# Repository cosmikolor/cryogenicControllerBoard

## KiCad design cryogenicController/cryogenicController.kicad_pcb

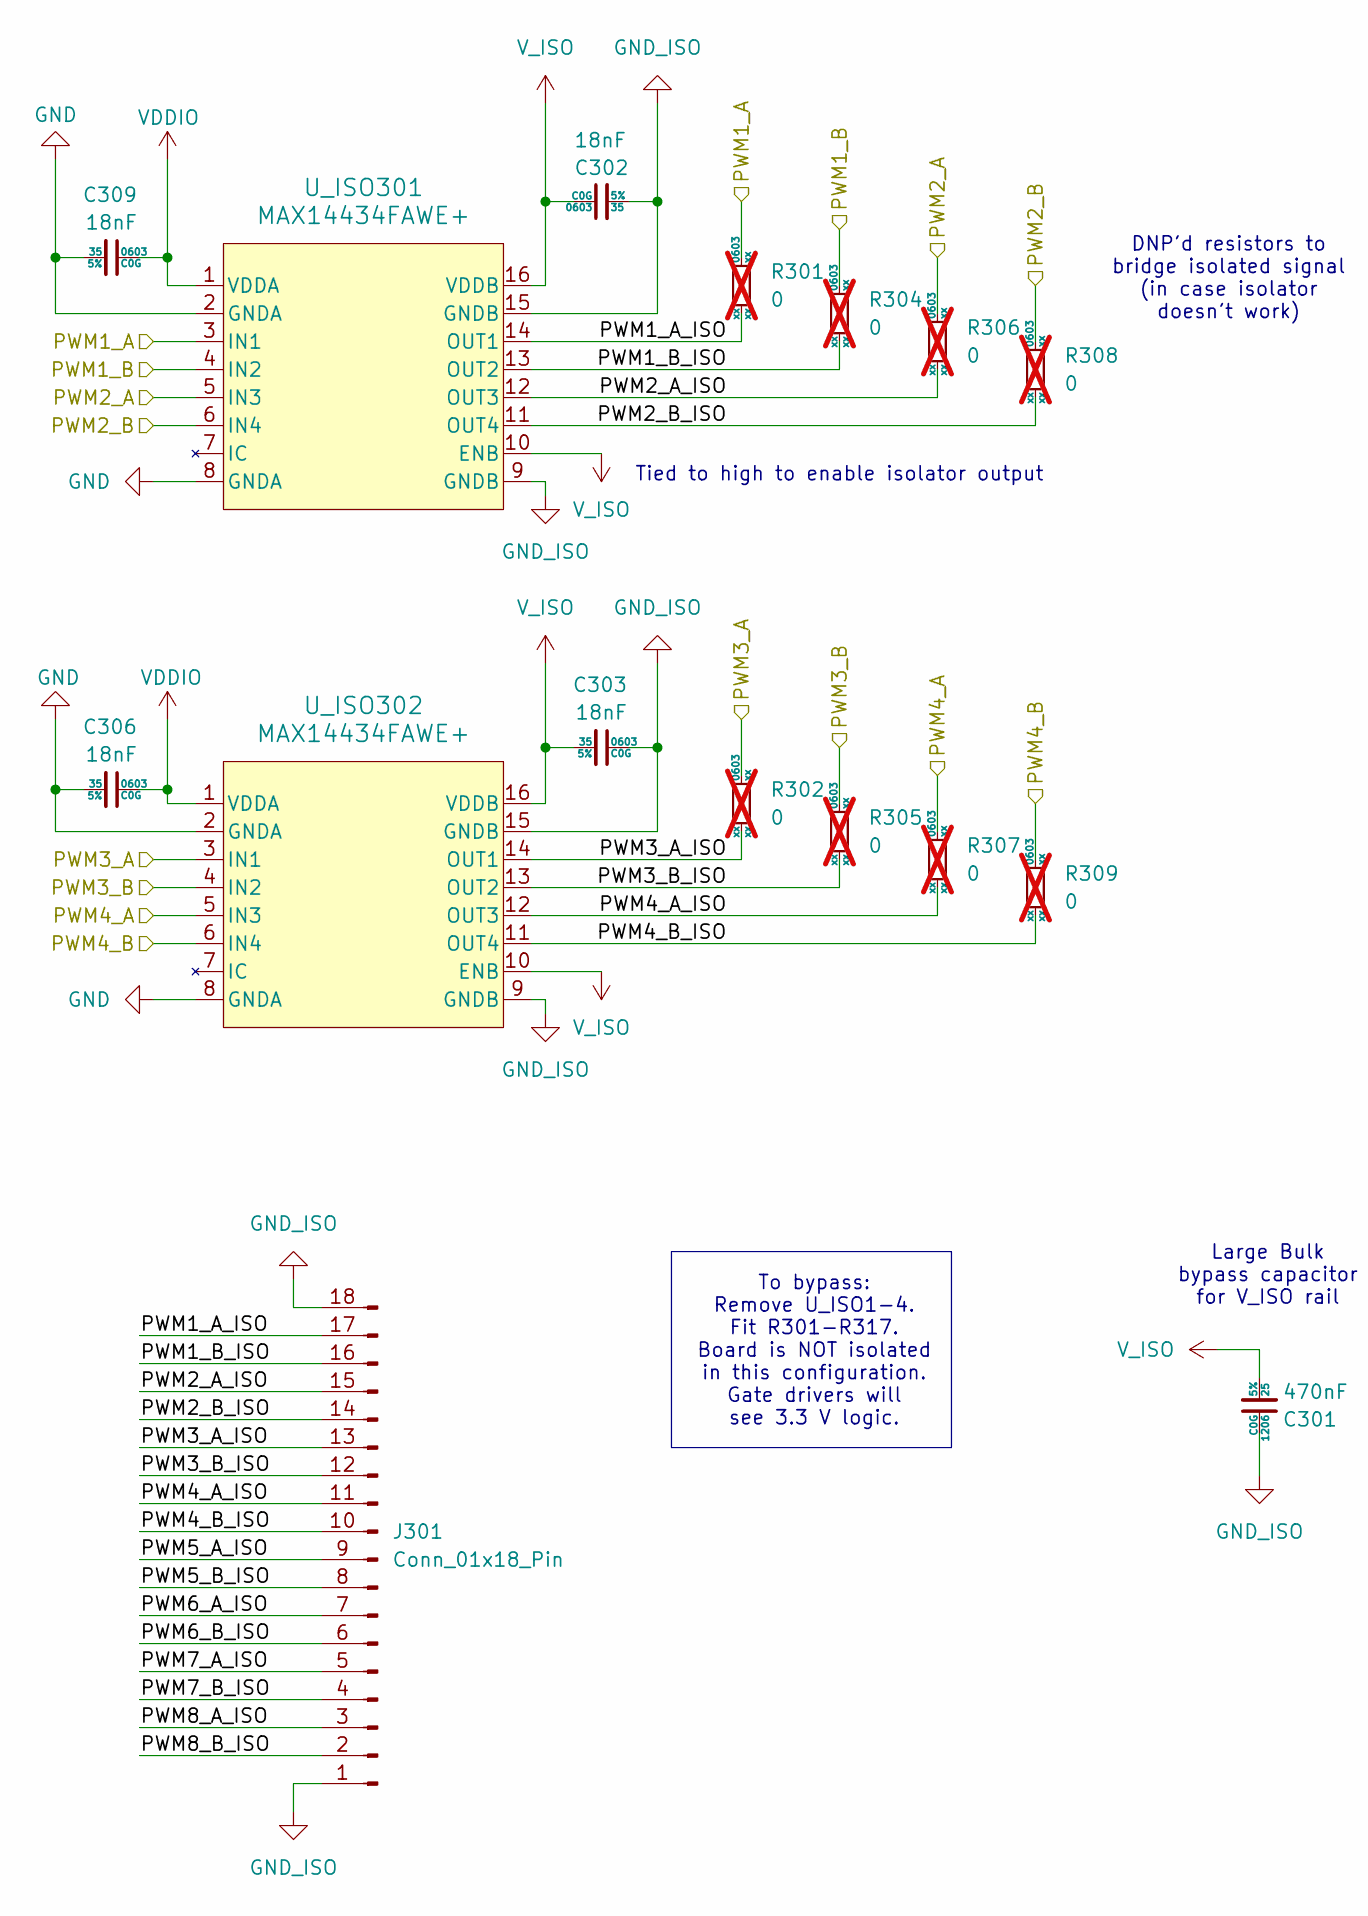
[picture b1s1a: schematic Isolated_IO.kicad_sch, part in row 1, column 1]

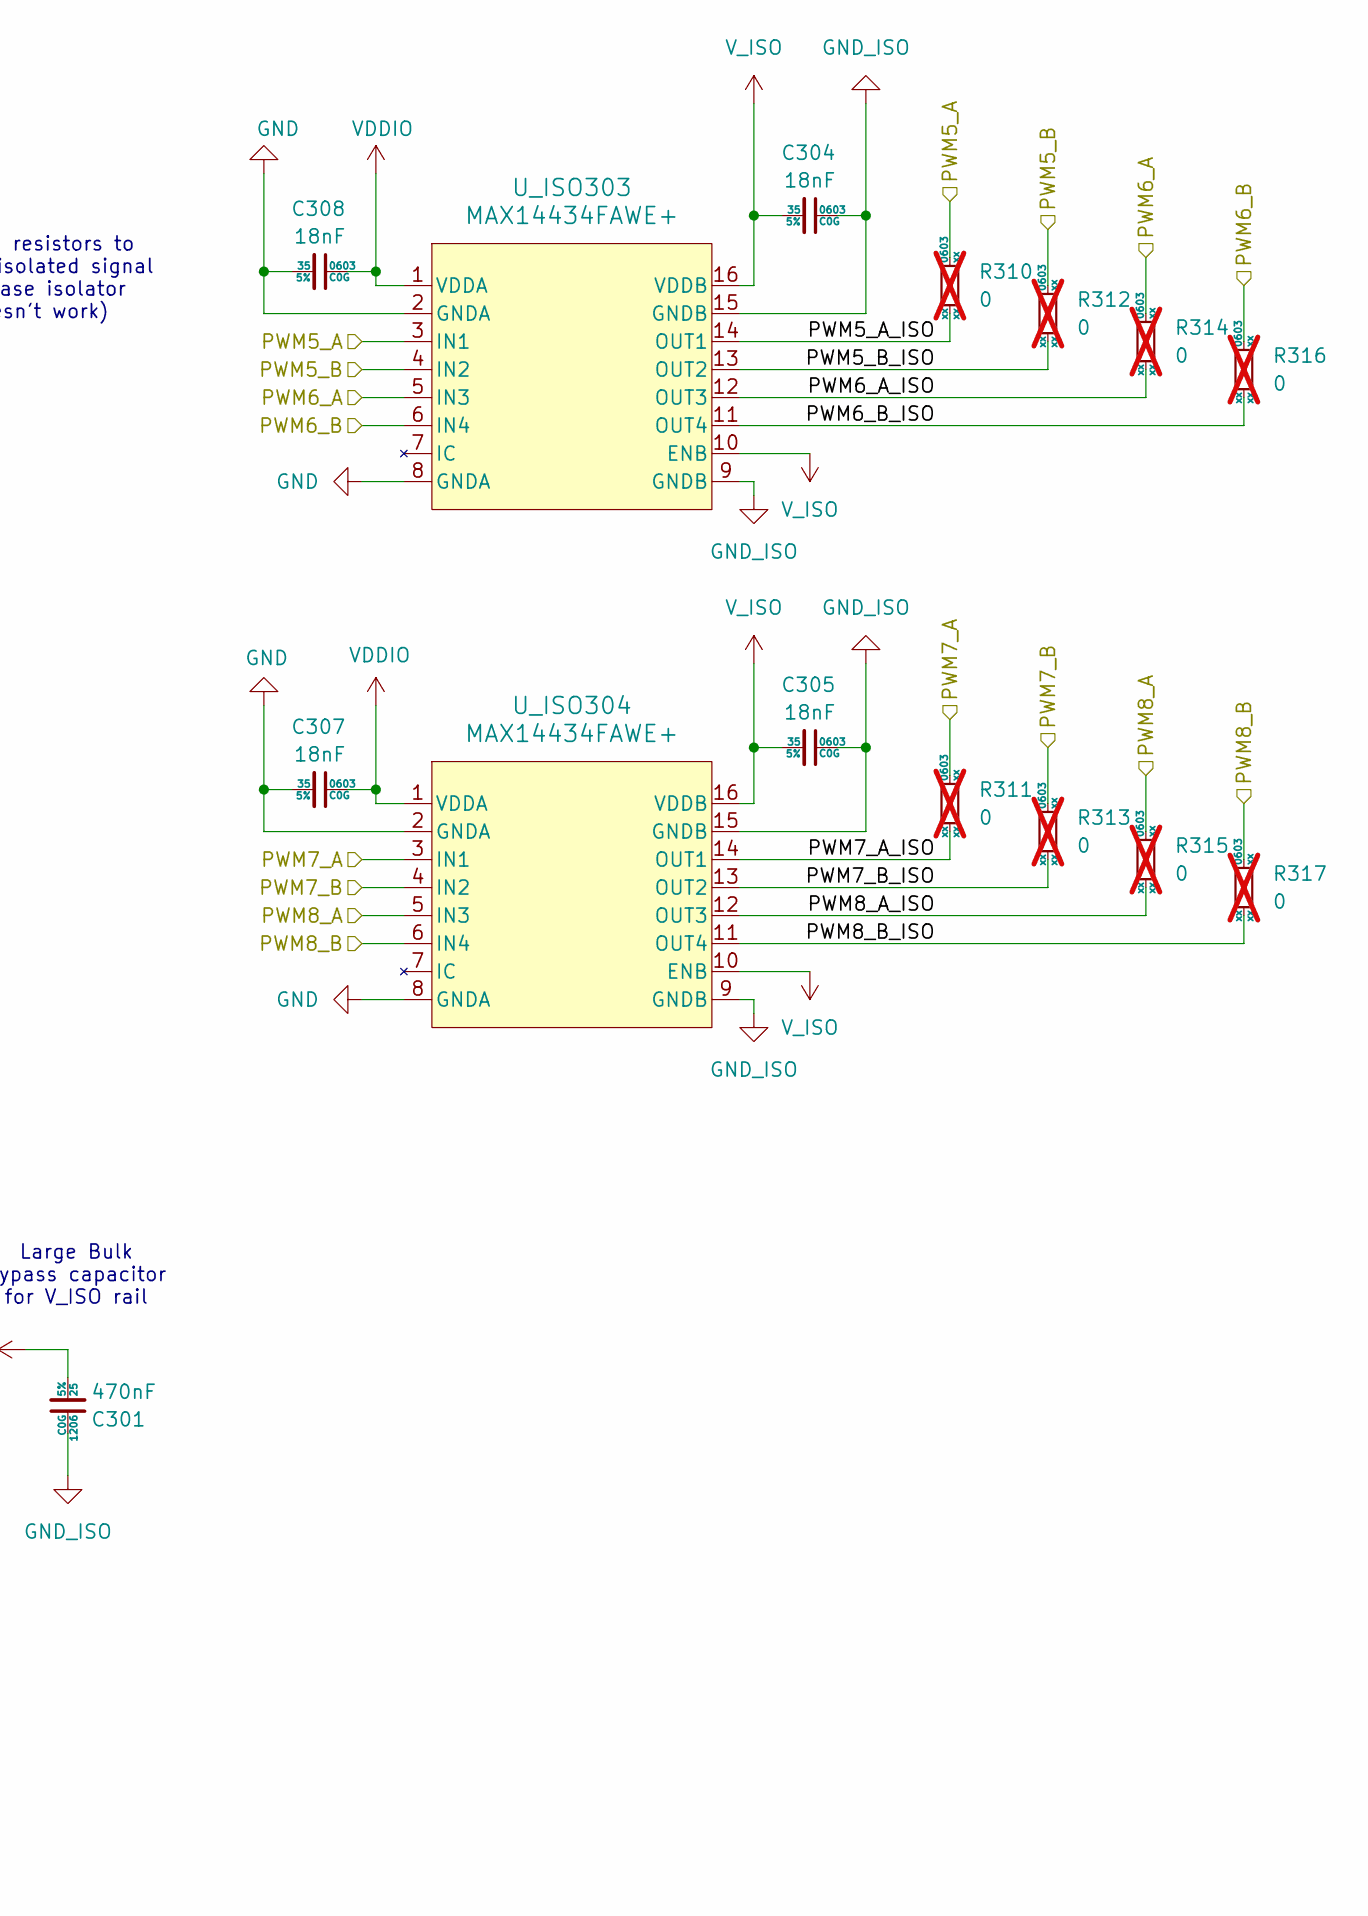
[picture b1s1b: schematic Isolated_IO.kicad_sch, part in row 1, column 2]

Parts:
C301: 470nF; C_1206_3216Metric; Voltage 25; Tolerance 5%; MfrPN GRM31C5C1E474JE01L
C302, C303, C304, C305, C306, C307, C308, C309: 18nF; C_0603_1608Metric; Voltage 35; Tolerance 5%; MfrPN C1608C0G1V183J080AC
J301: Conn_01x18_Pin; PinHeader_1x18_P2.54mm_Vertical
R301, R302, R304, R305, R306, R307, R308, R309, R310, R311, R312, R313, R314, R315, R316, R317: 0; R_1206_3216Metric; Tolerance xx; Voltage xx; not fitted
U_ISO301, U_ISO302, U_ISO303, U_ISO304: MAX14434FAWE+; SOIC-16W_7.5x10.3mm_P1.27mm

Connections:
/Isolated_IO/PWM1_A: R301.2, U_ISO301.3 (IN1); also elsewhere on the board
/Isolated_IO/PWM1_A_ISO: J301.17, R301.1, U_ISO301.14 (OUT1)
/Isolated_IO/PWM1_B: R304.2, U_ISO301.4 (IN2); also elsewhere on the board
/Isolated_IO/PWM1_B_ISO: J301.16, R304.1, U_ISO301.13 (OUT2)
/Isolated_IO/PWM2_A: R306.2, U_ISO301.5 (IN3); also elsewhere on the board
/Isolated_IO/PWM2_A_ISO: J301.15, R306.1, U_ISO301.12 (OUT3)
/Isolated_IO/PWM2_B: R308.2, U_ISO301.6 (IN4); also elsewhere on the board
/Isolated_IO/PWM2_B_ISO: J301.14, R308.1, U_ISO301.11 (OUT4)
/Isolated_IO/PWM3_A: R302.2, U_ISO302.3 (IN1); also elsewhere on the board
/Isolated_IO/PWM3_A_ISO: J301.13, R302.1, U_ISO302.14 (OUT1)
/Isolated_IO/PWM3_B: R305.2, U_ISO302.4 (IN2); also elsewhere on the board
/Isolated_IO/PWM3_B_ISO: J301.12, R305.1, U_ISO302.13 (OUT2)
/Isolated_IO/PWM4_A: R307.2, U_ISO302.5 (IN3); also elsewhere on the board
/Isolated_IO/PWM4_A_ISO: J301.11, R307.1, U_ISO302.12 (OUT3)
/Isolated_IO/PWM4_B: R309.2, U_ISO302.6 (IN4); also elsewhere on the board
/Isolated_IO/PWM4_B_ISO: J301.10, R309.1, U_ISO302.11 (OUT4)
/Isolated_IO/PWM5_A: R310.2, U_ISO303.3 (IN1); also elsewhere on the board
/Isolated_IO/PWM5_A_ISO: J301.9, R310.1, U_ISO303.14 (OUT1)
/Isolated_IO/PWM5_B: R312.2, U_ISO303.4 (IN2); also elsewhere on the board
/Isolated_IO/PWM5_B_ISO: J301.8, R312.1, U_ISO303.13 (OUT2)
/Isolated_IO/PWM6_A: R314.2, U_ISO303.5 (IN3); also elsewhere on the board
/Isolated_IO/PWM6_A_ISO: J301.7, R314.1, U_ISO303.12 (OUT3)
/Isolated_IO/PWM6_B: R316.2, U_ISO303.6 (IN4); also elsewhere on the board
/Isolated_IO/PWM6_B_ISO: J301.6, R316.1, U_ISO303.11 (OUT4)
/Isolated_IO/PWM7_A: R311.2, U_ISO304.3 (IN1); also elsewhere on the board
/Isolated_IO/PWM7_A_ISO: J301.5, R311.1, U_ISO304.14 (OUT1)
/Isolated_IO/PWM7_B: R313.2, U_ISO304.4 (IN2); also elsewhere on the board
/Isolated_IO/PWM7_B_ISO: J301.4, R313.1, U_ISO304.13 (OUT2)
/Isolated_IO/PWM8_A: R315.2, U_ISO304.5 (IN3); also elsewhere on the board
/Isolated_IO/PWM8_A_ISO: J301.3, R315.1, U_ISO304.12 (OUT3)
/Isolated_IO/PWM8_B: R317.2, U_ISO304.6 (IN4); also elsewhere on the board
/Isolated_IO/PWM8_B_ISO: J301.2, R317.1, U_ISO304.11 (OUT4)
GND: C306.2, C307.2, C308.2, C309.2, U_ISO301.2 (GNDA), U_ISO301.8 (GNDA), U_ISO302.2 (GNDA), U_ISO302.8 (GNDA), U_ISO303.2 (GNDA), U_ISO303.8 (GNDA), U_ISO304.2 (GNDA), U_ISO304.8 (GNDA); also elsewhere on the board
GND_ISO: C301.1, C302.2, C303.1, C304.1, C305.1, J301.1, J301.18, U_ISO301.9 (GNDB), U_ISO301.15 (GNDB), U_ISO302.9 (GNDB), U_ISO302.15 (GNDB), U_ISO303.9 (GNDB), U_ISO303.15 (GNDB), U_ISO304.9 (GNDB), U_ISO304.15 (GNDB); also elsewhere on the board
VDDIO: C306.1, C307.1, C308.1, C309.1, U_ISO301.1 (VDDA), U_ISO302.1 (VDDA), U_ISO303.1 (VDDA), U_ISO304.1 (VDDA); also elsewhere on the board
V_ISO: C301.2, C302.1, C303.2, C304.2, C305.2, U_ISO301.10 (ENB), U_ISO301.16 (VDDB), U_ISO302.10 (ENB), U_ISO302.16 (VDDB), U_ISO303.10 (ENB), U_ISO303.16 (VDDB), U_ISO304.10 (ENB), U_ISO304.16 (VDDB); also elsewhere on the board

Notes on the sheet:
DNP'd resistors to bridge isolated signal (in case isolator doesn't work)
To bypass: Remove U_ISO1-4. Fit R301-R317. Board is NOT isolated in this configuration. Gate drivers will see 3.3 V logic.
Tied to high to enable isolator output
Large Bulk bypass capacitor for V_ISO rail

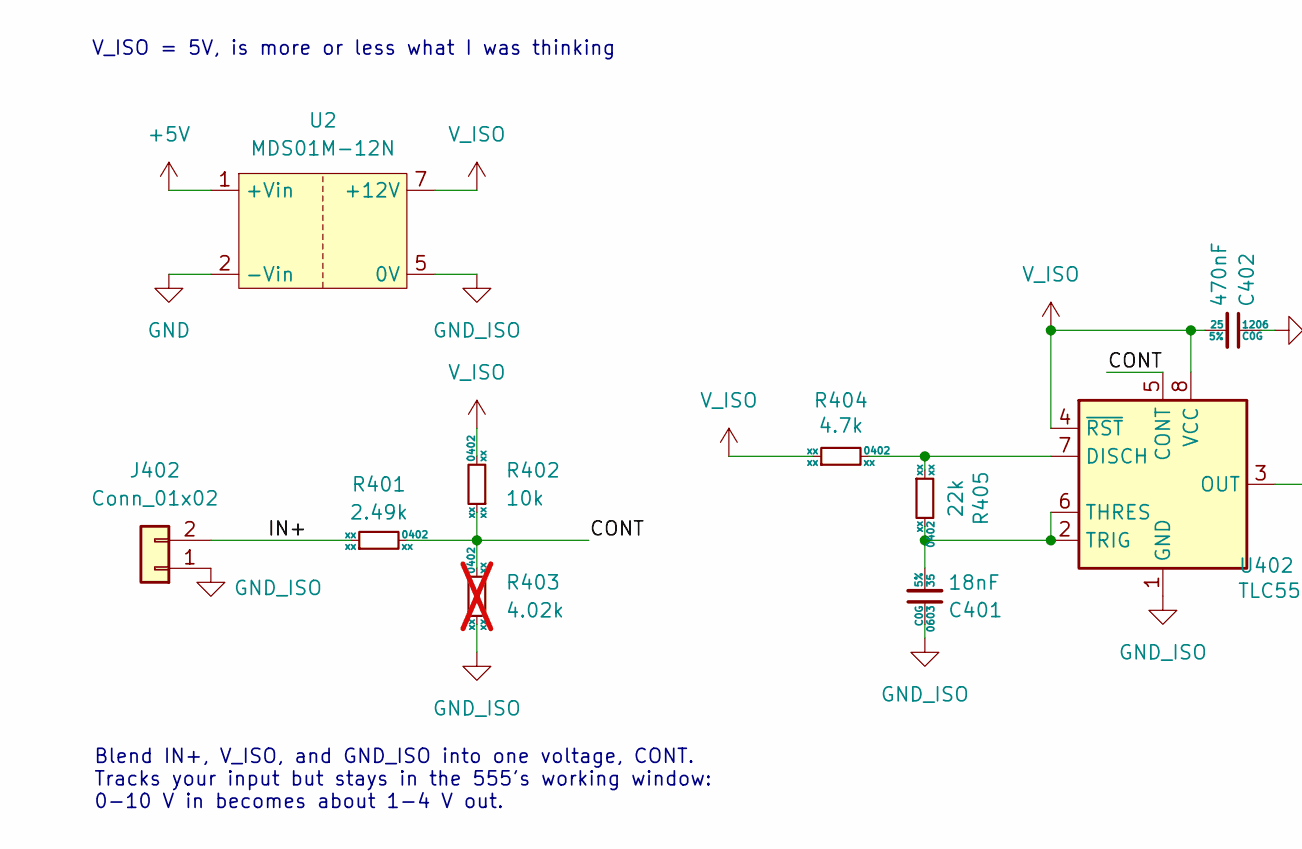
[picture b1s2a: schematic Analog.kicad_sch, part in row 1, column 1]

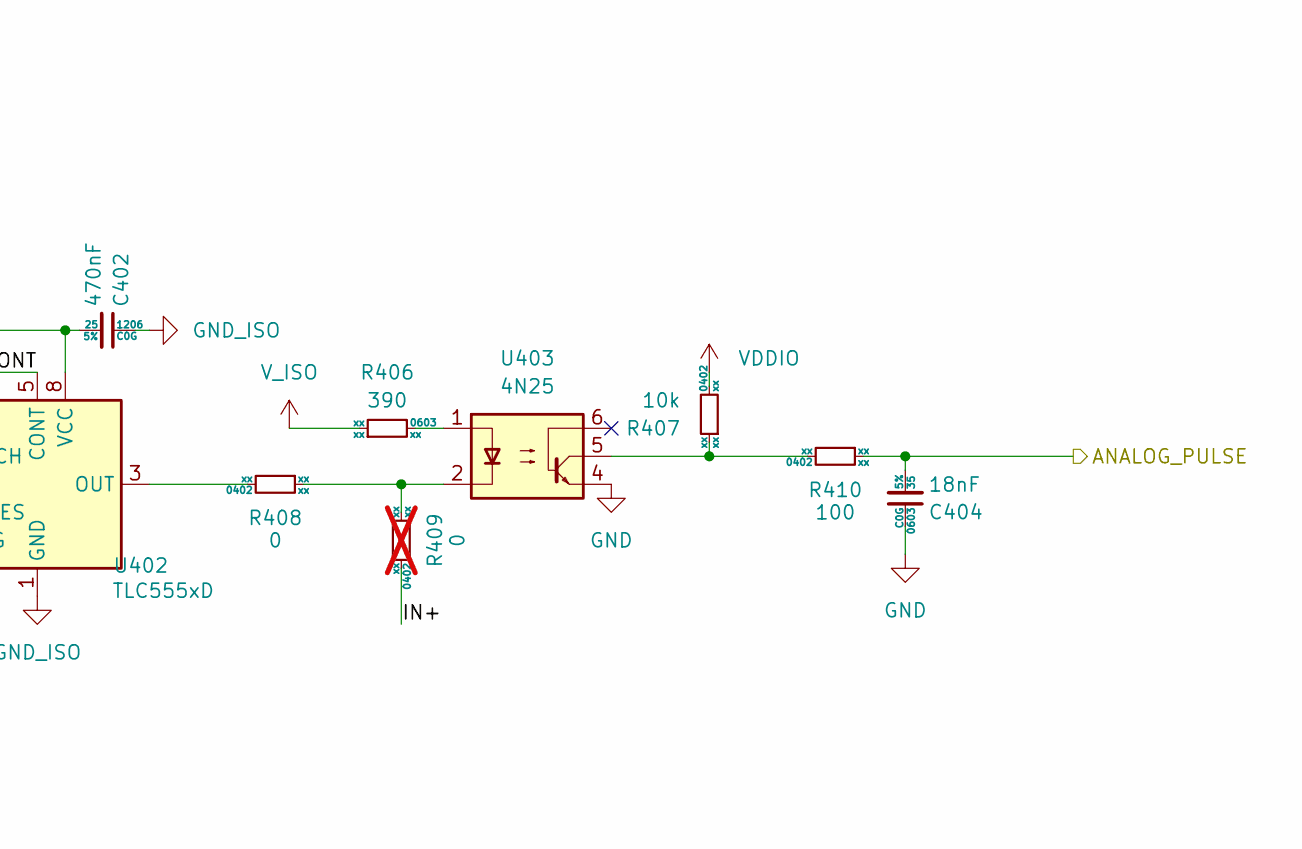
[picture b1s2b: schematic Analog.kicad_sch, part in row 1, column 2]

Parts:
C401, C404: 18nF; C_0603_1608Metric; Voltage 35; Tolerance 5%
C402: 470nF; C_1206_3216Metric; Voltage 25; Tolerance 5%; MfrPN GRM31C5C1E474JE01L
J402: Conn_01x02; PinHeader_1x02_P2.54mm_Vertical
R401: 2.49k; R_0402_1005Metric; Tolerance xx; Voltage xx
R402, R407: 10k; R_0402_1005Metric; Tolerance xx; Voltage xx
R403: 4.02k; R_0402_1005Metric; Tolerance xx; Voltage xx; not fitted
R404: 4.7k; R_0402_1005Metric; Tolerance xx; Voltage xx
R405: 22k; R_0402_1005Metric; Tolerance xx; Voltage xx
R406: 390; R_0402_1005Metric; Tolerance xx; Voltage xx
R408: 0; R_0402_1005Metric; Tolerance xx; Voltage xx
R409: 0; R_0402_1005Metric; Tolerance xx; Voltage xx; not fitted
R410: 100; R_0402_1005Metric; Tolerance xx; Voltage xx
U2: MDS01M-12N
U402: TLC555xD; SOIC-8_3.9x4.9mm_P1.27mm
U403: 4N25; DIP-6_W7.62mm

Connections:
+5V: U2.1 (+Vin)
/Analog/ANALOG_PULSE: C404.2, R410.1; also elsewhere on the board
/Analog/CONT: R401.2, R402.1, R403.2, U402.5 (CONT)
/Analog/IN+: J402.2, R401.1, R409.2
GND: C404.1, U2.2 (-Vin), U403.4; also elsewhere on the board
GND_ISO: C401.1, C402.1, J402.1, R403.1, U2.5 (0V), U402.1 (GND); also elsewhere on the board
unnamed: R406.2, U403.1
unnamed: R407.1, R410.2, U403.5
unnamed: R408.1, R409.1, U403.2
unnamed: R404.2, R405.1, U402.7 (DISCH)
unnamed: R408.2, U402.3 (OUT)
unnamed: C401.2, R405.2, U402.2 (TRIG), U402.6 (THRES)
VDDIO: R407.2; also elsewhere on the board
V_ISO: C402.2, R402.2, R404.1, R406.1, U2.7 (+12V), U402.4 (~RST), U402.8 (VCC); also elsewhere on the board

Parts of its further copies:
C403, C406, C407, C409: 18nF; C_0603_1608Metric; Voltage 35; Tolerance 5%
C405, C408: 470nF; C_1206_3216Metric; Voltage 25; Tolerance 5%; MfrPN GRM31C5C1E474JE01L
J403, J404: Conn_01x02; PinHeader_1x02_P2.54mm_Vertical
R411, R421: 2.49k; R_0402_1005Metric; Tolerance xx; Voltage xx
R412, R419, R422, R429: 10k; R_0402_1005Metric; Tolerance xx; Voltage xx
R413, R423: 4.02k; R_0402_1005Metric; Tolerance xx; Voltage xx; not fitted
R414, R424: 4.7k; R_0402_1005Metric; Tolerance xx; Voltage xx
R415, R425: 22k; R_0402_1005Metric; Tolerance xx; Voltage xx
R416, R426: 0; R_0402_1005Metric; Tolerance xx; Voltage xx
R417, R427: 390; R_0402_1005Metric; Tolerance xx; Voltage xx
R418, R428: 0; R_0402_1005Metric; Tolerance xx; Voltage xx; not fitted
R420, R430: 100; R_0402_1005Metric; Tolerance xx; Voltage xx
U404, U406: TLC555xD; SOIC-8_3.9x4.9mm_P1.27mm
U405, U407: 4N25; DIP-6_W7.62mm

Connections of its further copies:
/Analog1/ANALOG_PULSE: C406.2, R420.1; also elsewhere on the board
/Analog1/CONT: R411.2, R412.1, R413.2, U404.5 (CONT)
/Analog1/IN+: J403.2, R411.1, R418.2
/Analog2/ANALOG_PULSE: C409.2, R430.1; also elsewhere on the board
/Analog2/CONT: R421.2, R422.1, R423.2, U406.5 (CONT)
/Analog2/IN+: J404.2, R421.1, R428.2
GND: C406.1, C409.1, U405.4, U407.4; also elsewhere on the board
GND_ISO: C403.1, C405.1, C407.1, C408.1, J403.1, J404.1, R413.1, R423.1, U404.1 (GND), U406.1 (GND); also elsewhere on the board
unnamed: R416.1, R418.1, U405.2
unnamed: R417.2, U405.1
unnamed: R419.1, R420.2, U405.5
unnamed: R426.1, R428.1, U407.2
unnamed: R427.2, U407.1
unnamed: R429.1, R430.2, U407.5
unnamed: R414.2, R415.1, U404.7 (DISCH)
unnamed: R416.2, U404.3 (OUT)
unnamed: C403.2, R415.2, U404.2 (TRIG), U404.6 (THRES)
unnamed: R424.2, R425.1, U406.7 (DISCH)
unnamed: R426.2, U406.3 (OUT)
unnamed: C407.2, R425.2, U406.2 (TRIG), U406.6 (THRES)
VDDIO: R419.2, R429.2; also elsewhere on the board
V_ISO: C405.2, C408.2, R412.2, R414.1, R417.1, R422.2, R424.1, R427.1, U404.4 (~RST), U404.8 (VCC), U406.4 (~RST), U406.8 (VCC); also elsewhere on the board

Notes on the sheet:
Blend IN+, V_ISO, and GND_ISO into one voltage, CONT. Tracks your input but stays in the 555's working window: 0-10 V in becomes about 1-4 V out.
V_ISO = 5V, is more or less what I was thinking

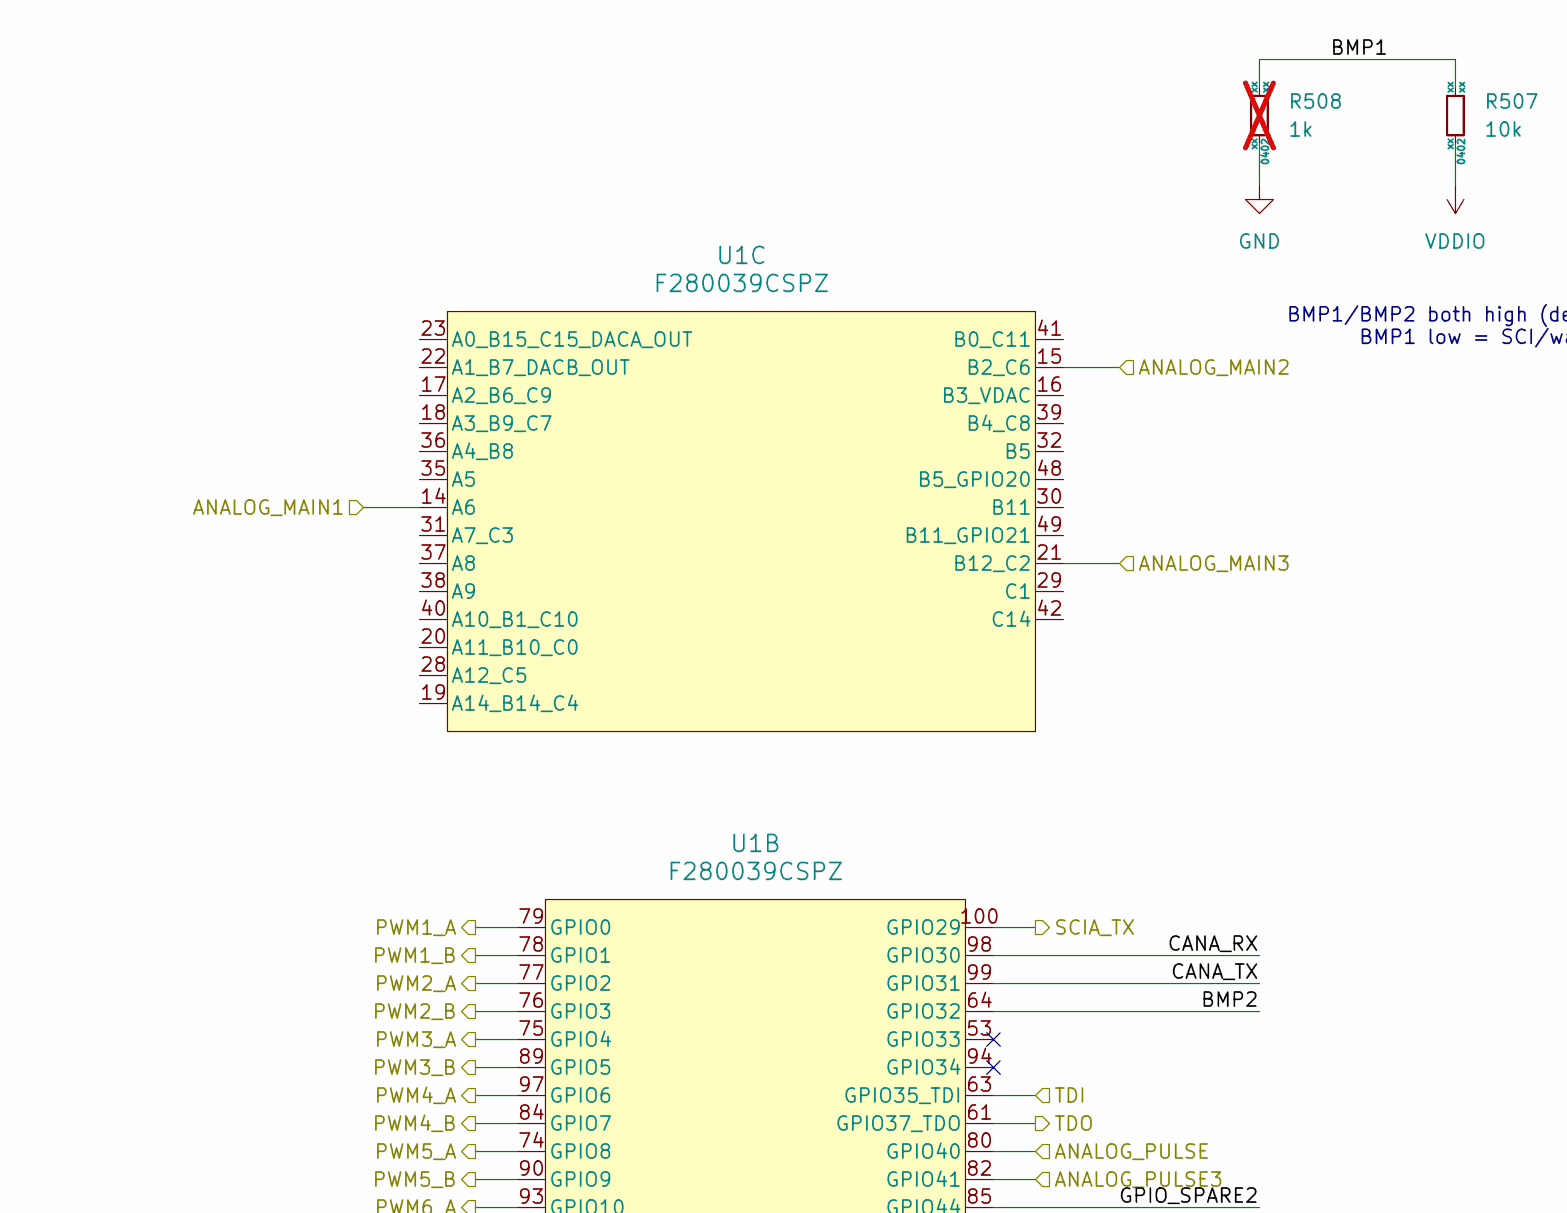
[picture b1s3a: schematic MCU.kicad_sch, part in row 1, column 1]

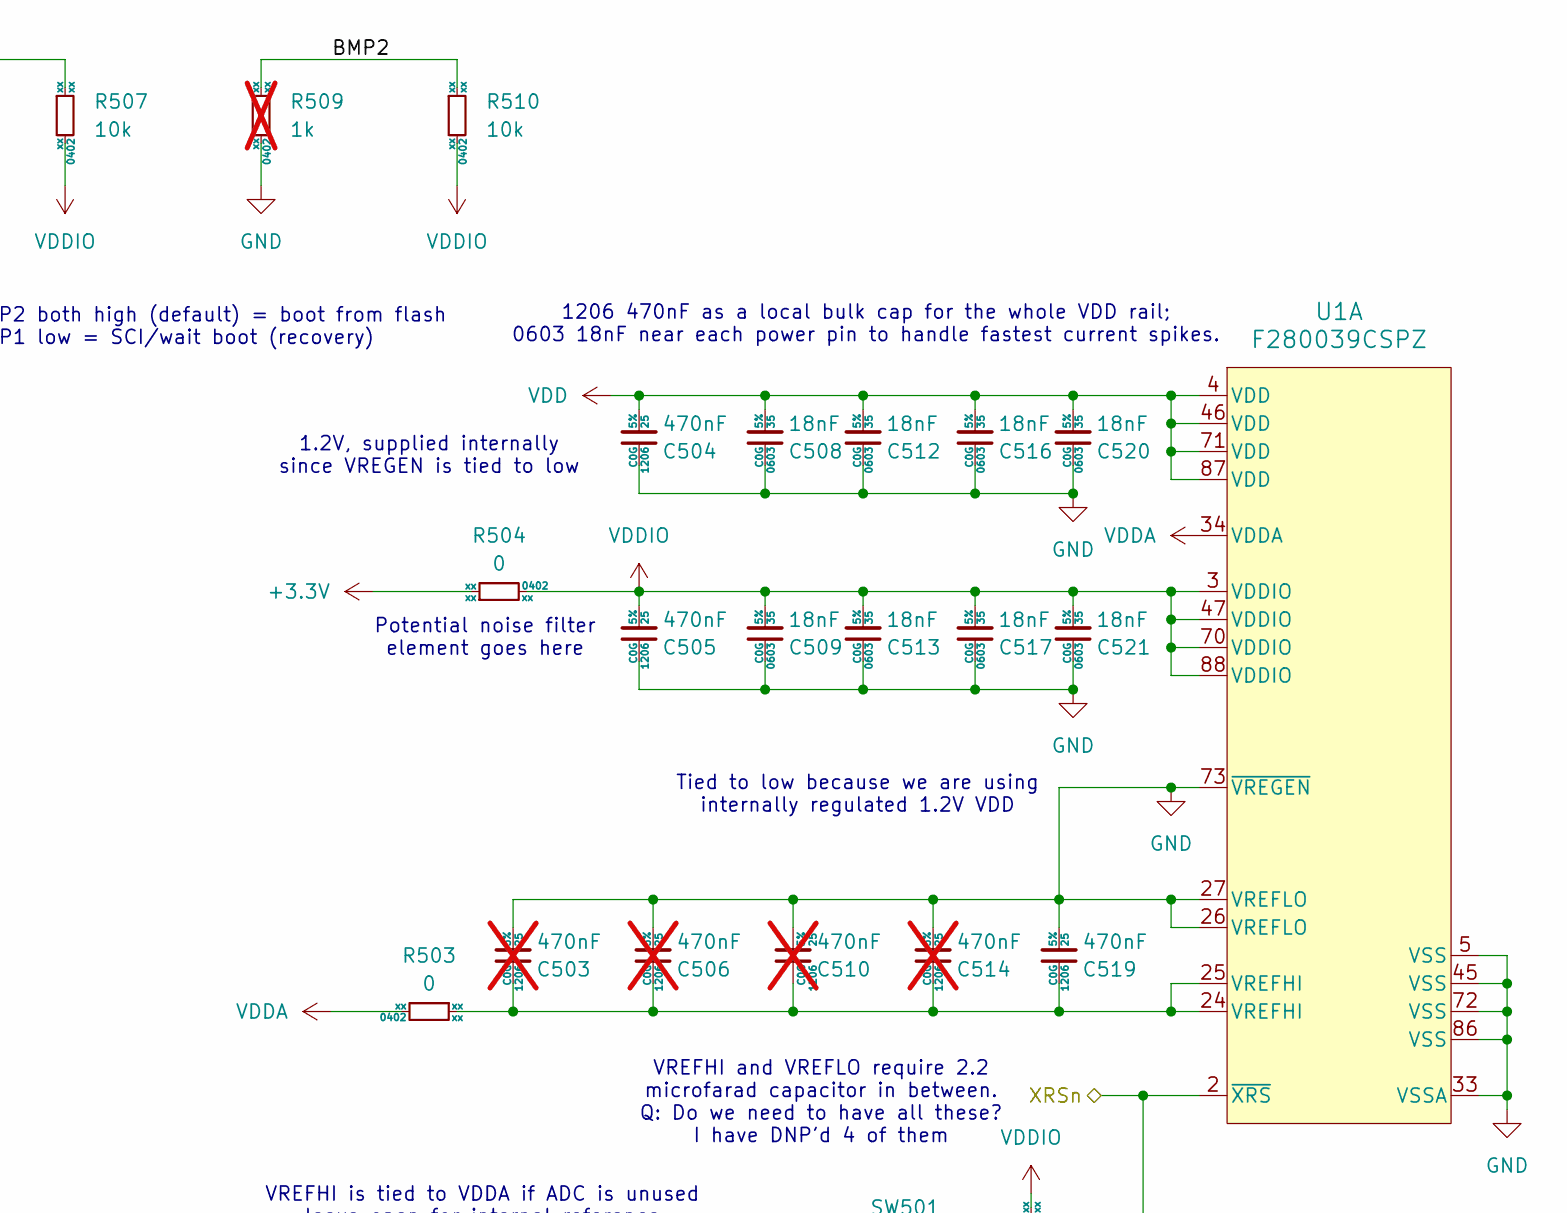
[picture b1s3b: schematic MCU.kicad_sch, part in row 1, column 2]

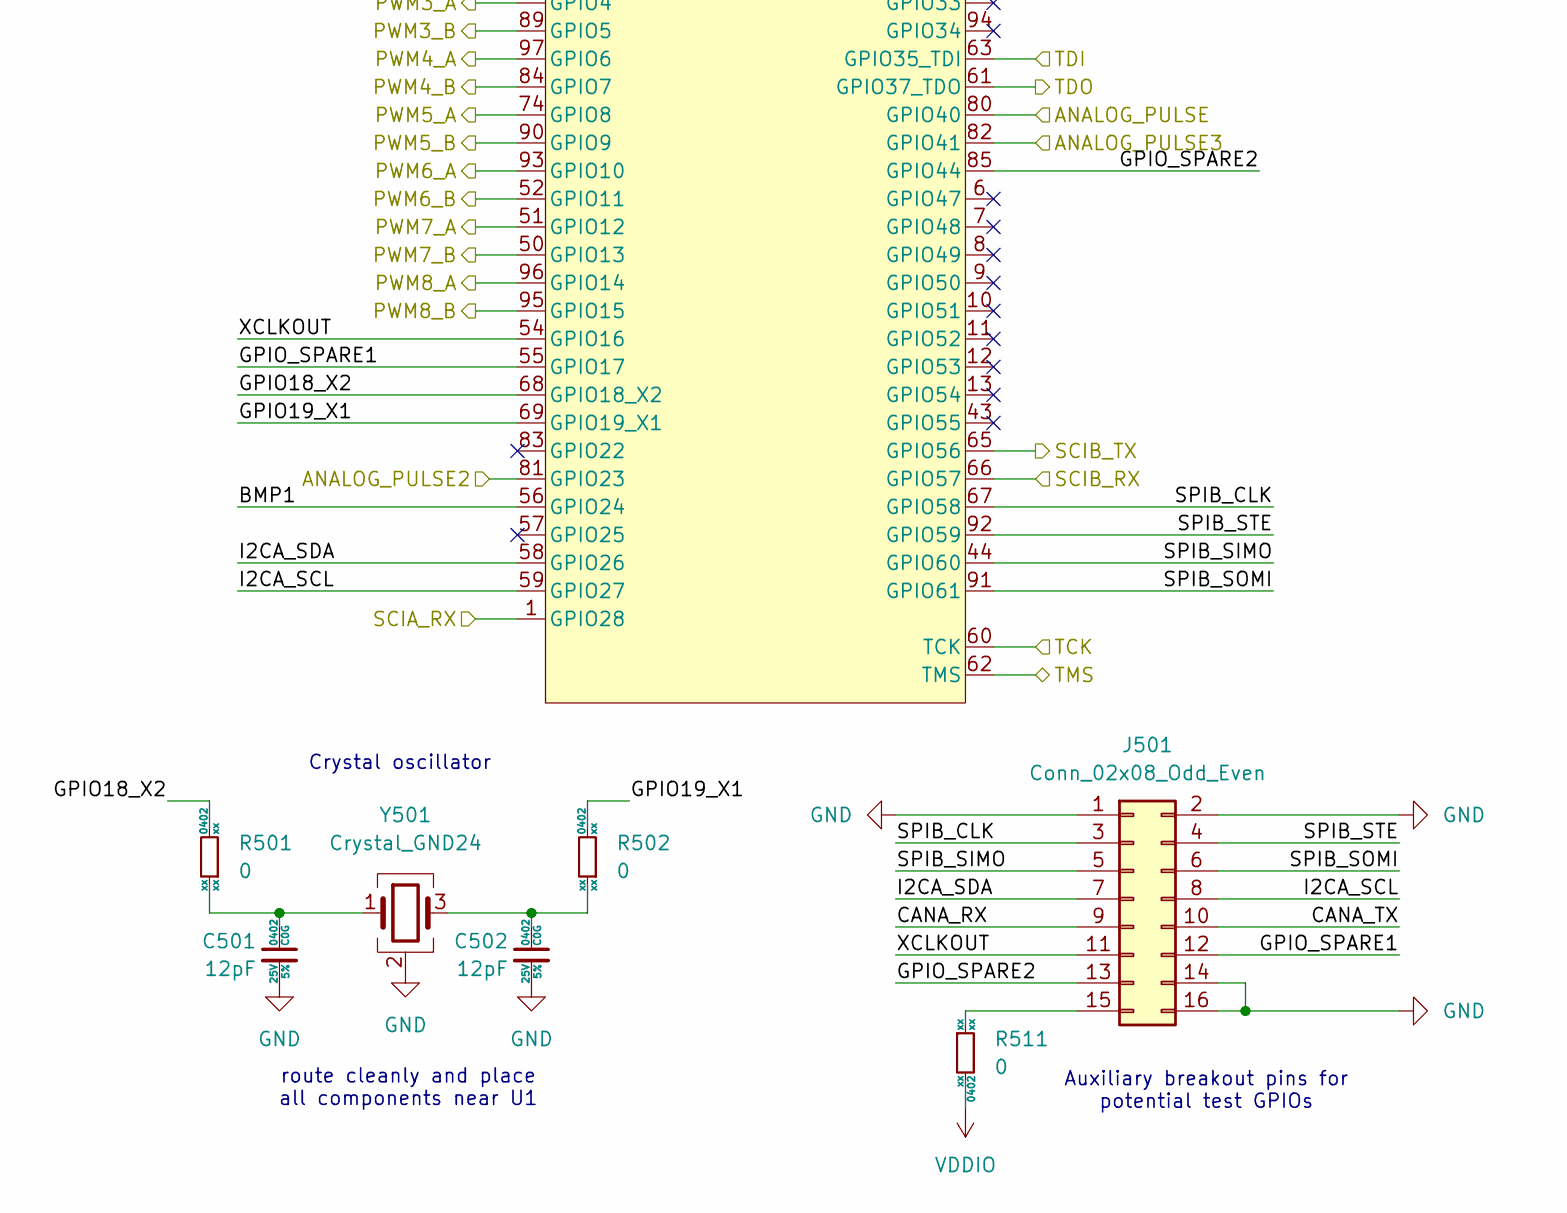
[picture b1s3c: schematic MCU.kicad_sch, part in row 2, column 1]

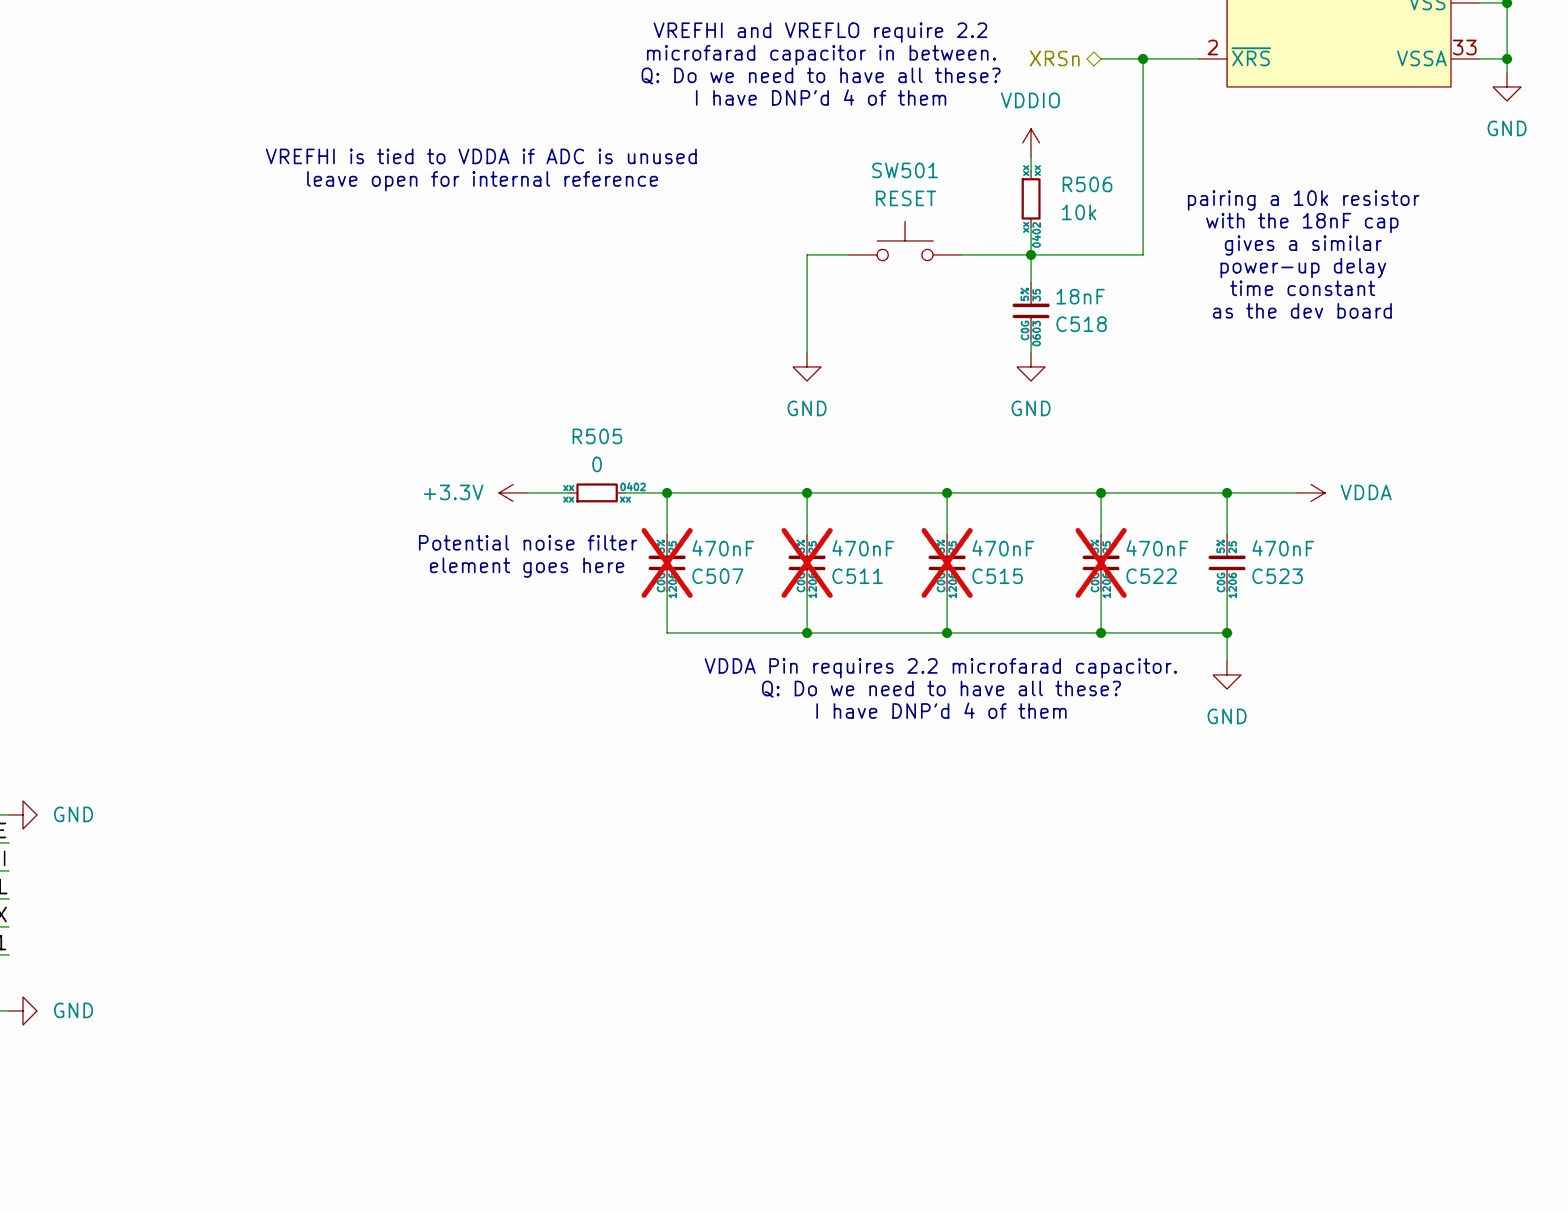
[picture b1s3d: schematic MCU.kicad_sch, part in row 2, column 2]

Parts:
C501, C502: 12pF; C_0402_1005Metric; Voltage 25V; Tolerance 5%; MfrPN GRT1555C1E120JA02D
C503, C506, C507, C510, C511, C514, C515, C522: 470nF; C_1206_3216Metric; Voltage 25; Tolerance 5%; not fitted
C504, C505, C519, C523: 470nF; C_1206_3216Metric; Voltage 25; Tolerance 5%; MfrPN GRM31C5C1E474JE01L
C508, C509, C512, C513, C516, C517, C520, C521: 18nF; C_0603_1608Metric; Voltage 35; Tolerance 5%; MfrPN C1608C0G1V183J080AC
C518: 18nF; C_0603_1608Metric; Voltage 35; Tolerance 5%
J501: Conn_02x08_Odd_Even; PinHeader_2x08_P2.54mm_Vertical
R501, R502, R503, R504, R505, R511: 0; R_0402_1005Metric; Tolerance xx; Voltage xx
R506, R507, R510: 10k; R_0402_1005Metric; Tolerance xx; Voltage xx
R508, R509: 1k; R_0402_1005Metric; Tolerance xx; Voltage xx; not fitted
SW501: RESET; SW_SPST_TL3342
U1: F280039CSPZ; F280039CSPZR
Y501: Crystal_GND24; Crystal_SMD_3225-4Pin_3.2x2.5mm

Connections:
+3.3V: R504.1, R505.1; also elsewhere on the board
/Analog1/ANALOG_PULSE: U1.81 (GPIO23); also elsewhere on the board
/Analog2/ANALOG_PULSE: U1.82 (GPIO41); also elsewhere on the board
/Analog/ANALOG_PULSE: U1.80 (GPIO40); also elsewhere on the board
/Analog_Board1/ANALOG_MAIN: U1.15 (B2_C6); also elsewhere on the board
/Analog_Board2/ANALOG_MAIN: U1.21 (B12_C2); also elsewhere on the board
/Analog_Board/ANALOG_MAIN: U1.14 (A6); also elsewhere on the board
/Isolated_IO/PWM1_A: U1.79 (GPIO0); also elsewhere on the board
/Isolated_IO/PWM1_B: U1.78 (GPIO1); also elsewhere on the board
/Isolated_IO/PWM2_A: U1.77 (GPIO2); also elsewhere on the board
/Isolated_IO/PWM2_B: U1.76 (GPIO3); also elsewhere on the board
/Isolated_IO/PWM3_A: U1.75 (GPIO4); also elsewhere on the board
/Isolated_IO/PWM3_B: U1.89 (GPIO5); also elsewhere on the board
/Isolated_IO/PWM4_A: U1.97 (GPIO6); also elsewhere on the board
/Isolated_IO/PWM4_B: U1.84 (GPIO7); also elsewhere on the board
/Isolated_IO/PWM5_A: U1.74 (GPIO8); also elsewhere on the board
/Isolated_IO/PWM5_B: U1.90 (GPIO9); also elsewhere on the board
/Isolated_IO/PWM6_A: U1.93 (GPIO10); also elsewhere on the board
/Isolated_IO/PWM6_B: U1.52 (GPIO11); also elsewhere on the board
/Isolated_IO/PWM7_A: U1.51 (GPIO12); also elsewhere on the board
/Isolated_IO/PWM7_B: U1.50 (GPIO13); also elsewhere on the board
/Isolated_IO/PWM8_A: U1.96 (GPIO14); also elsewhere on the board
/Isolated_IO/PWM8_B: U1.95 (GPIO15); also elsewhere on the board
/JTAG_UART/SCIA_RX: U1.1 (GPIO28); also elsewhere on the board
/JTAG_UART/SCIA_TX: U1.100 (GPIO29); also elsewhere on the board
/JTAG_UART/SCIB_RX: U1.66 (GPIO57); also elsewhere on the board
/JTAG_UART/SCIB_TX: U1.65 (GPIO56); also elsewhere on the board
/JTAG_UART/TCK: U1.60 (TCK); also elsewhere on the board
/JTAG_UART/TDI: U1.63 (GPIO35_TDI); also elsewhere on the board
/JTAG_UART/TDO: U1.61 (GPIO37_TDO); also elsewhere on the board
/JTAG_UART/TMS: U1.62 (TMS); also elsewhere on the board
/JTAG_UART/XRSn: C518.2, R506.2, SW501.2, U1.2 (~XRS); also elsewhere on the board
/MCU/BMP1: R507.1, R508.1, U1.56 (GPIO24)
/MCU/BMP2: R509.1, R510.1, U1.64 (GPIO32)
/MCU/CANA_RX: J501.9, U1.98 (GPIO30)
/MCU/CANA_TX: J501.10, U1.99 (GPIO31)
/MCU/GPIO18_X2: R501.2, U1.68 (GPIO18_X2)
/MCU/GPIO19_X1: R502.2, U1.69 (GPIO19_X1)
/MCU/GPIO_SPARE1: J501.12, U1.55 (GPIO17)
/MCU/GPIO_SPARE2: J501.13, U1.85 (GPIO44)
/MCU/I2CA_SCL: J501.8, U1.59 (GPIO27)
/MCU/I2CA_SDA: J501.7, U1.58 (GPIO26)
/MCU/SPIB_CLK: J501.3, U1.67 (GPIO58)
/MCU/SPIB_SIMO: J501.5, U1.44 (GPIO60)
/MCU/SPIB_SOMI: J501.6, U1.91 (GPIO61)
/MCU/SPIB_STE: J501.4, U1.92 (GPIO59)
/MCU/XCLKOUT: J501.11, U1.54 (GPIO16)
GND: C501.2, C502.2, C503.2, C504.1, C505.1, C506.2, C507.1, C508.1, C509.1, C510.2, C511.1, C512.1, C513.1, C514.2, C515.1, C516.1, C517.1, C518.1, C519.2, C520.1, C521.1, C522.1, C523.1, J501.1, J501.2, J501.14, J501.16, R508.2, R509.2, SW501.1, U1.5 (VSS), U1.26 (VREFLO), U1.27 (VREFLO), U1.33 (VSSA), U1.45 (VSS), U1.72 (VSS), U1.73 (~VREGEN), U1.86 (VSS), Y501.2 (G), Y501.4 (G); also elsewhere on the board
unnamed: C501.1, R501.1, Y501.1
unnamed: C502.1, R502.1, Y501.3
unnamed: C503.1, C506.1, C510.1, C514.1, C519.1, R503.1, U1.24 (VREFHI), U1.25 (VREFHI)
unnamed: J501.15, R511.1
VDD: C504.2, C508.2, C512.2, C516.2, C520.2, U1.4 (VDD), U1.46 (VDD), U1.71 (VDD), U1.87 (VDD)
VDDA: C507.2, C511.2, C515.2, C522.2, C523.2, R503.2, R505.2, U1.34 (VDDA)
VDDIO: C505.2, C509.2, C513.2, C517.2, C521.2, R504.2, R506.1, R507.2, R510.2, R511.2, U1.3 (VDDIO), U1.47 (VDDIO), U1.70 (VDDIO), U1.88 (VDDIO); also elsewhere on the board

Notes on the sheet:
Tied to low because we are using internally regulated 1.2V VDD
VREFHI is tied to VDDA if ADC is unused leave open for internal reference
Crystal oscillator
1206 470nF as a local bulk cap for the whole VDD rail; 0603 18nF near each power pin to handle fastest current spikes.
VDDA Pin requires 2.2 microfarad capacitor. Q: Do we need to have all these? I have DNP'd 4 of them
route cleanly and place all components near U1
1.2V, supplied internally since VREGEN is tied to low
BMP1/BMP2 both high (default) = boot from flash BMP1 low = SCI/wait boot (recovery)
VREFHI and VREFLO require 2.2 microfarad capacitor in between. Q: Do we need to have all these? I have DNP'd 4 of them
Auxiliary breakout pins for potential test GPIOs
Potential noise filter element goes here
pairing a 10k resistor with the 18nF cap gives a similar power-up delay time constant as the dev board
